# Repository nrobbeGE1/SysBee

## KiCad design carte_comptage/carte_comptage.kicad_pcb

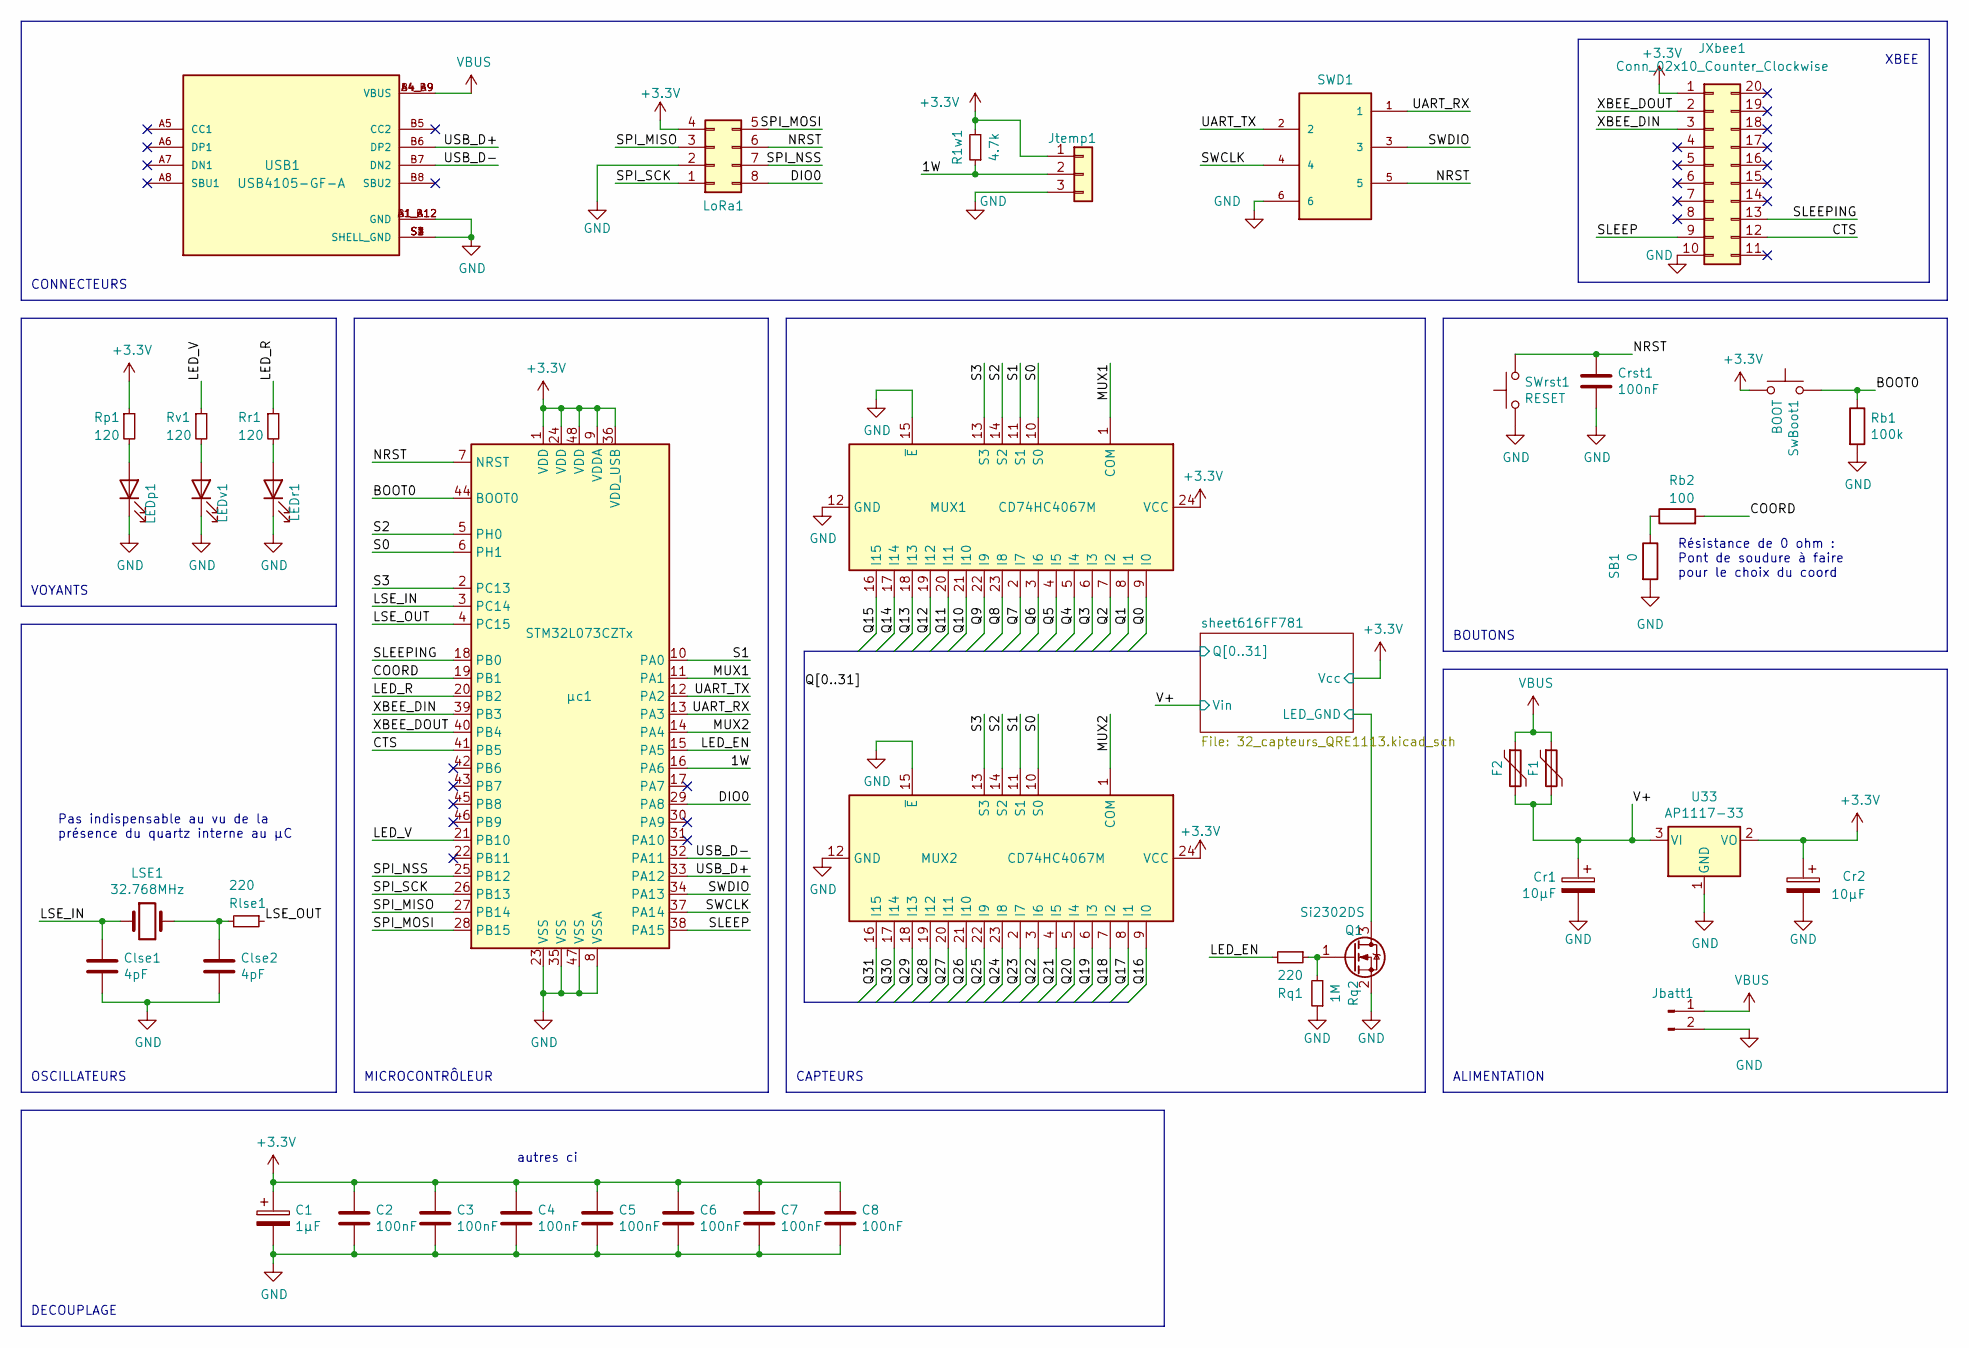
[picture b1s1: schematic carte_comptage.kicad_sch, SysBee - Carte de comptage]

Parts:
C1: 1µF; C_1206_3216Metric
C2, C3, C4, C5, C6, C7, C8: 100nF; C_1206_3216Metric
Clse1, Clse2: 4pF; C_1206_3216Metric
Cr1, Cr2: 10µF; CP_EIA-3216-18_Kemet-A
Crst1: 100nF; C_1206_3216Metric
F1, F2: Polyfuse; R_1206_3216Metric
JXbee1: Conn_02x10_Counter_Clockwise; Connector_Xbee
Jbatt1: Conn_01x02_Male; JST_PH_B2B-PH-K_1x02_P2.00mm_Vertical
Jtemp1: 1 WIRE; JST_PH_B3B-PH-K_1x03_P2.00mm_Vertical
LEDp1: LED; D_1206_3216Metric
LEDr1: LED; D_1206_3216Metric
LEDv1: LED; D_1206_3216Metric
LSE1: 32.768MHz; Crystal_SMD_2012-2Pin_2.0x1.2mm
LoRa1: Conn_02x04_Counter_Clockwise; ConnectorMicromatch-8
MUX1, MUX2: CD74HC4067M; SOIC-24W_7.5x15.4mm_P1.27mm
Q1: Si2302DS; SOT-23
R1w1: 4.7k; R_1206_3216Metric
Rb1: 100k; R_1206_3216Metric
Rb2: 100; R_1206_3216Metric
Rlse1: 220; R_1206_3216Metric
Rp1: 120; R_1206_3216Metric
Rq1: 220; R_1206_3216Metric
Rq2: 1M; R_1206_3216Metric
Rr1: 120; R_1206_3216Metric
Rv1: 120; R_1206_3216Metric
SB1: 0; SolderJumper-2_P1.3mm_Open_TrianglePad1.0x1.5mm
SWD1: SWD; TE_7-188275-6
SWrst1: RESET; PinHeader_1x02_P2.54mm_Vertical
SwBoot1: BOOT; PinHeader_1x02_P2.54mm_Vertical
U33: AP1117-33; SOT-223-3_TabPin2
USB1: USB4105-GF-A; GCT_USB4105-GF-A; PARTREV A3
µc1: STM32L073CZTx; LQFP-48_7x7mm_P0.5mm

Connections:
+3V3: C1.1, C2.1, C3.1, C4.1, C5.1, C6.1, C7.1, C8.1, Cr2.1, JXbee1.1, Jtemp1.1, LoRa1.4, MUX1.24 (VCC), MUX2.24 (VCC), R1w1.2, Rp1.1, SwBoot1.1, U33.2 (VO), µc1.1 (VDD), µc1.9 (VDDA), µc1.24 (VDD), µc1.36 (VDD_USB), µc1.48 (VDD); also elsewhere on the board
/1W: Jtemp1.2, R1w1.1, µc1.16 (PA6)
/BOOT0: Rb1.1, SwBoot1.2, µc1.44 (BOOT0)
/COORD: Rb2.2, µc1.19 (PB1)
/CTS: JXbee1.12, µc1.41 (PB5)
/DIO0: LoRa1.8, µc1.29 (PA8)
/LED_EN: Rq1.2, µc1.15 (PA5)
/LED_R: Rr1.1, µc1.20 (PB2)
/LED_V: Rv1.1, µc1.21 (PB10)
/LSE_IN: Clse1.1, LSE1.1, µc1.3 (PC14)
/LSE_OUT: Rlse1.1, µc1.4 (PC15)
/MUX1: MUX1.1 (COM), µc1.11 (PA1)
/MUX2: MUX2.1 (COM), µc1.14 (PA4)
/NRST: Crst1.1, LoRa1.6, SWD1.5, SWrst1.2, µc1.7 (NRST)
/Q0: MUX1.9 (I0); also elsewhere on the board
/Q1: MUX1.8 (I1); also elsewhere on the board
/Q2: MUX1.7 (I2); also elsewhere on the board
/Q3: MUX1.6 (I3); also elsewhere on the board
/Q4: MUX1.5 (I4); also elsewhere on the board
/Q5: MUX1.4 (I5); also elsewhere on the board
/Q6: MUX1.3 (I6); also elsewhere on the board
/Q7: MUX1.2 (I7); also elsewhere on the board
/Q8: MUX1.23 (I8); also elsewhere on the board
/Q9: MUX1.22 (I9); also elsewhere on the board
/Q10: MUX1.21 (I10); also elsewhere on the board
/Q11: MUX1.20 (I11); also elsewhere on the board
/Q12: MUX1.19 (I12); also elsewhere on the board
/Q13: MUX1.18 (I13); also elsewhere on the board
/Q14: MUX1.17 (I14); also elsewhere on the board
/Q15: MUX1.16 (I15); also elsewhere on the board
/Q16: MUX2.9 (I0); also elsewhere on the board
/Q17: MUX2.8 (I1); also elsewhere on the board
/Q18: MUX2.7 (I2); also elsewhere on the board
/Q19: MUX2.6 (I3); also elsewhere on the board
/Q20: MUX2.5 (I4); also elsewhere on the board
/Q21: MUX2.4 (I5); also elsewhere on the board
/Q22: MUX2.3 (I6); also elsewhere on the board
/Q23: MUX2.2 (I7); also elsewhere on the board
/Q24: MUX2.23 (I8); also elsewhere on the board
/Q25: MUX2.22 (I9); also elsewhere on the board
/Q26: MUX2.21 (I10); also elsewhere on the board
/Q27: MUX2.20 (I11); also elsewhere on the board
/Q28: MUX2.19 (I12); also elsewhere on the board
/Q29: MUX2.18 (I13); also elsewhere on the board
/Q30: MUX2.17 (I14); also elsewhere on the board
/Q31: MUX2.16 (I15); also elsewhere on the board
/S0: MUX1.10 (S0), MUX2.10 (S0), µc1.6 (PH1)
/S1: MUX1.11 (S1), MUX2.11 (S1), µc1.10 (PA0)
/S2: MUX1.14 (S2), MUX2.14 (S2), µc1.5 (PH0)
/S3: MUX1.13 (S3), MUX2.13 (S3), µc1.2 (PC13)
/SLEEP: JXbee1.9, µc1.38 (PA15)
/SLEEPING: JXbee1.13, µc1.18 (PB0)
/SPI_MISO: LoRa1.3, µc1.27 (PB14)
/SPI_MOSI: LoRa1.5, µc1.28 (PB15)
/SPI_NSS: LoRa1.7, µc1.25 (PB12)
/SPI_SCK: LoRa1.1, µc1.26 (PB13)
/SWCLK: SWD1.4, µc1.37 (PA14)
/SWDIO: SWD1.3, µc1.34 (PA13)
/UART_RX: SWD1.1, µc1.13 (PA3)
/UART_TX: SWD1.2, µc1.12 (PA2)
/USB_D+: USB1.B6 (DP2), µc1.33 (PA12)
/USB_D-: USB1.B7 (DN2), µc1.32 (PA11)
/V+: Cr1.1, F1.2, F2.2, U33.3 (VI); also elsewhere on the board
/XBEE_DIN: JXbee1.3, µc1.39 (PB3)
/XBEE_DOUT: JXbee1.2, µc1.40 (PB4)
/sheet616FF781/LED_GND: Q1.3 (D); also elsewhere on the board
GND: C1.2, C2.2, C3.2, C4.2, C5.2, C6.2, C7.2, C8.2, Clse1.2, Clse2.2, Cr1.2, Cr2.2, Crst1.2, JXbee1.10, Jbatt1.2, Jtemp1.3, LEDp1.1 (K), LEDr1.1 (K), LEDv1.1 (K), LoRa1.2, MUX1.12 (GND), MUX1.15 (~E), MUX2.12 (GND), MUX2.15 (~E), Q1.2 (S), Rb1.2, Rq2.1, SB1.2, SWD1.6, SWrst1.1, U33.1 (GND), USB1.A1_B12 (GND), USB1.B1_A12 (GND), USB1.S1 (SHELL_GND), USB1.S2 (SHELL_GND), USB1.S3 (SHELL_GND), USB1.S4 (SHELL_GND), µc1.8 (VSSA), µc1.23 (VSS), µc1.35 (VSS), µc1.47 (VSS); also elsewhere on the board
unnamed: Clse2.1, LSE1.2, Rlse1.2
unnamed: LEDp1.2 (A), Rp1.2
unnamed: LEDr1.2 (A), Rr1.2
unnamed: LEDv1.2 (A), Rv1.2
unnamed: Q1.1 (G), Rq1.1, Rq2.2
unnamed: Rb2.1, SB1.1
VBUS: F1.1, F2.1, Jbatt1.1, USB1.A4_B9 (VBUS), USB1.B4_A9 (VBUS)

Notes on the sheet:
OSCILLATEURS
DECOUPLAGE
ALIMENTATION
VOYANTS
BOUTONS
Résistance de 0 ohm : Pont de soudure à faire pour le choix du coord
CONNECTEURS
MICROCONTRÔLEUR
autres ci
Pas indispensable au vu de la présence du quartz interne au µC
XBEE
CAPTEURS

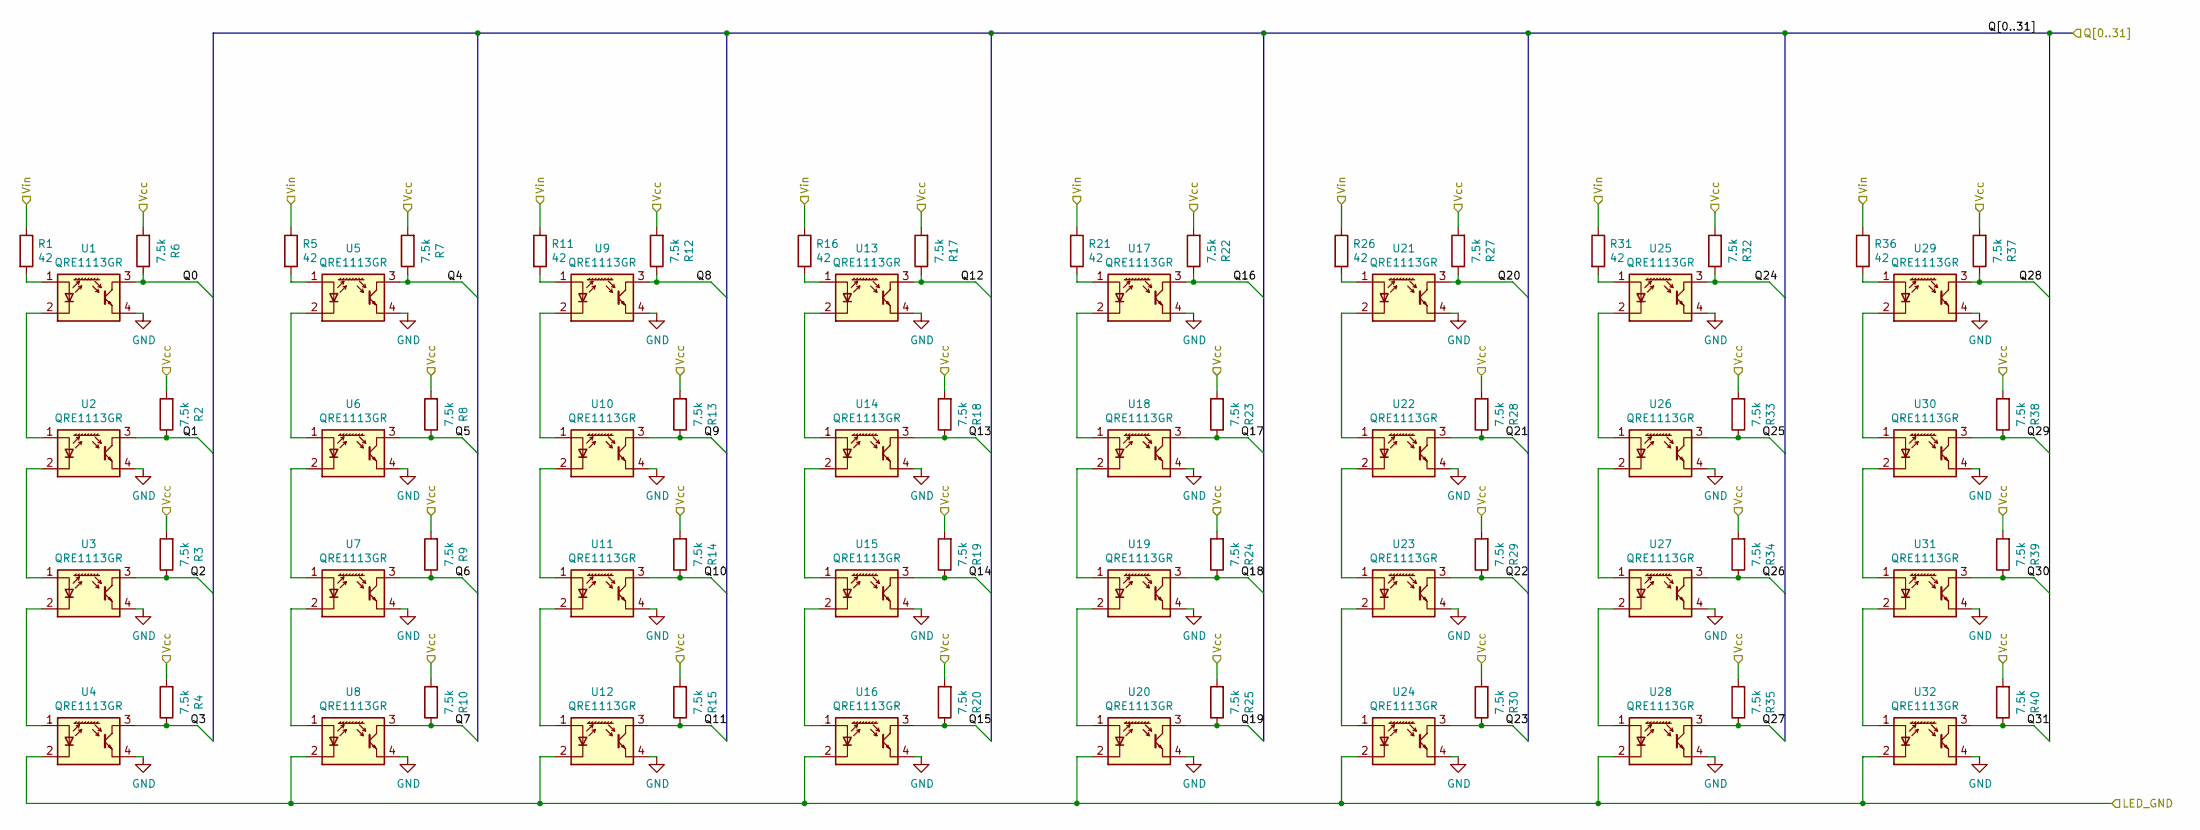
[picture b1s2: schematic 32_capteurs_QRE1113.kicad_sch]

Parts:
R1, R5, R11, R16, R21, R26, R31, R36: 42; R_1206_3216Metric
R2, R3, R4, R6, R7, R8, R9, R10, R12, R13, R14, R15, R17, R18, R19, R20, R22, R23, R24, R25, R27, R28, R29, R30, R32, R33, R34, R35, R37, R38, R39, R40: 7.5k; R_1206_3216Metric
U1, U2, U3, U4, U5, U6, U7, U8, U9, U10, U11, U12, U13, U14, U15, U16, U17, U18, U19, U20, U21, U22, U23, U24, U25, U26, U27, U28, U29, U30, U31, U32: QRE1113GR; OnSemi_CASE100CY

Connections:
+3V3: R2.2, R3.2, R4.2, R6.2, R7.2, R8.2, R9.2, R10.2, R12.2, R13.2, R14.2, R15.2, R17.2, R18.2, R19.2, R20.2, R22.2, R23.2, R24.2, R25.2, R27.2, R28.2, R29.2, R30.2, R32.2, R33.2, R34.2, R35.2, R37.2, R38.2, R39.2, R40.2; also elsewhere on the board
/Q0: R6.1, U1.3; also elsewhere on the board
/Q1: R2.1, U2.3; also elsewhere on the board
/Q2: R3.1, U3.3; also elsewhere on the board
/Q3: R4.1, U4.3; also elsewhere on the board
/Q4: R7.1, U5.3; also elsewhere on the board
/Q5: R8.1, U6.3; also elsewhere on the board
/Q6: R9.1, U7.3; also elsewhere on the board
/Q7: R10.1, U8.3; also elsewhere on the board
/Q8: R12.1, U9.3; also elsewhere on the board
/Q9: R13.1, U10.3; also elsewhere on the board
/Q10: R14.1, U11.3; also elsewhere on the board
/Q11: R15.1, U12.3; also elsewhere on the board
/Q12: R17.1, U13.3; also elsewhere on the board
/Q13: R18.1, U14.3; also elsewhere on the board
/Q14: R19.1, U15.3; also elsewhere on the board
/Q15: R20.1, U16.3; also elsewhere on the board
/Q16: R22.1, U17.3; also elsewhere on the board
/Q17: R23.1, U18.3; also elsewhere on the board
/Q18: R24.1, U19.3; also elsewhere on the board
/Q19: R25.1, U20.3; also elsewhere on the board
/Q20: R27.1, U21.3; also elsewhere on the board
/Q21: R28.1, U22.3; also elsewhere on the board
/Q22: R29.1, U23.3; also elsewhere on the board
/Q23: R30.1, U24.3; also elsewhere on the board
/Q24: R32.1, U25.3; also elsewhere on the board
/Q25: R33.1, U26.3; also elsewhere on the board
/Q26: R34.1, U27.3; also elsewhere on the board
/Q27: R35.1, U28.3; also elsewhere on the board
/Q28: R37.1, U29.3; also elsewhere on the board
/Q29: R38.1, U30.3; also elsewhere on the board
/Q30: R39.1, U31.3; also elsewhere on the board
/Q31: R40.1, U32.3; also elsewhere on the board
/V+: R1.1, R5.1, R11.1, R16.1, R21.1, R26.1, R31.1, R36.1; also elsewhere on the board
/sheet616FF781/LED_GND: U4.2 (K), U8.2 (K), U12.2 (K), U16.2 (K), U20.2 (K), U24.2 (K), U28.2 (K), U32.2 (K); also elsewhere on the board
GND: U1.4, U2.4, U3.4, U4.4, U5.4, U6.4, U7.4, U8.4, U9.4, U10.4, U11.4, U12.4, U13.4, U14.4, U15.4, U16.4, U17.4, U18.4, U19.4, U20.4, U21.4, U22.4, U23.4, U24.4, U25.4, U26.4, U27.4, U28.4, U29.4, U30.4, U31.4, U32.4; also elsewhere on the board
unnamed: R1.2, U1.1 (A)
unnamed: R5.2, U5.1 (A)
unnamed: R11.2, U9.1 (A)
unnamed: R16.2, U13.1 (A)
unnamed: R21.2, U17.1 (A)
unnamed: R26.2, U21.1 (A)
unnamed: R31.2, U25.1 (A)
unnamed: R36.2, U29.1 (A)
unnamed: U1.2 (K), U2.1 (A)
unnamed: U2.2 (K), U3.1 (A)
unnamed: U3.2 (K), U4.1 (A)
unnamed: U5.2 (K), U6.1 (A)
unnamed: U6.2 (K), U7.1 (A)
unnamed: U7.2 (K), U8.1 (A)
unnamed: U9.2 (K), U10.1 (A)
unnamed: U10.2 (K), U11.1 (A)
unnamed: U11.2 (K), U12.1 (A)
unnamed: U13.2 (K), U14.1 (A)
unnamed: U14.2 (K), U15.1 (A)
unnamed: U15.2 (K), U16.1 (A)
unnamed: U17.2 (K), U18.1 (A)
unnamed: U18.2 (K), U19.1 (A)
unnamed: U19.2 (K), U20.1 (A)
unnamed: U21.2 (K), U22.1 (A)
unnamed: U22.2 (K), U23.1 (A)
unnamed: U23.2 (K), U24.1 (A)
unnamed: U25.2 (K), U26.1 (A)
unnamed: U26.2 (K), U27.1 (A)
unnamed: U27.2 (K), U28.1 (A)
unnamed: U29.2 (K), U30.1 (A)
unnamed: U30.2 (K), U31.1 (A)
unnamed: U31.2 (K), U32.1 (A)

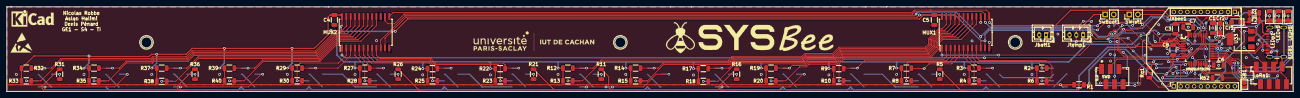
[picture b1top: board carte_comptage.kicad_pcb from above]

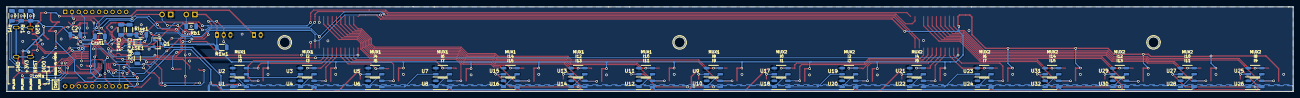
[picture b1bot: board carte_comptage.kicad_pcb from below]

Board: 2 copper layers, 380.0 x 25.0 mm, 115 parts (45 on the bottom side), 106 nets.

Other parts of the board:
Ref**: Val**; drawing

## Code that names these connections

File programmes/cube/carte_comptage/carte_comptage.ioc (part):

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Mcu.Name=STM32L073C(B-Z)Tx
Mcu.Package=LQFP48
Mcu.UserName=STM32L073CZTx
PA0.GPIOParameters=GPIO_Label
PA0.GPIO_Label=S1
PA0.Signal=GPIO_Output
PA1.GPIOParameters=GPIO_Label
PA1.GPIO_Label=MUX1
PA1.Signal=GPIO_Input
PA11.Mode=Device
PA11.Signal=USB_DM
PA12.Mode=Device
PA12.Signal=USB_DP
PA13.Mode=Serial_Wire
PA13.Signal=SYS_SWDIO
PA14.Mode=Serial_Wire
PA14.Signal=SYS_SWCLK
PA15.GPIOParameters=GPIO_Label
PA15.GPIO_Label=XBEE_SLEEP
PA15.Signal=GPIO_Output
PA2.Mode=Asynchronous
PA2.Signal=USART2_TX
PA3.Mode=Asynchronous
PA3.Signal=USART2_RX
PA4.GPIOParameters=GPIO_Label
PA4.GPIO_Label=MUX2
PA4.Signal=GPIO_Input
PA5.GPIOParameters=GPIO_Label
PA5.GPIO_Label=LED_EN
PA5.Signal=GPIO_Output
PA6.GPIOParameters=GPIO_Label
PA6.GPIO_Label=ONE_WIRE
PA6.Signal=GPIO_Input
PA8.GPIOParameters=GPIO_Label
PA8.GPIO_Label=DIO0
PA8.Signal=GPIO_Output
PB0.GPIOParameters=GPIO_Label
PB0.GPIO_Label=XBEE_SLEEPING
PB0.Signal=GPIO_Input
PB10.GPIOParameters=GPIO_Label
PB10.GPIO_Label=LED_V
PB10.Signal=GPIO_Output
PB11.GPIOParameters=GPIO_Label
PB11.GPIO_Label=ONE_WIRE
PB11.Signal=GPIO_Output
PB12.Mode=NSS_Signal_Hard_Output
PB12.Signal=SPI2_NSS
PB13.Mode=Full_Duplex_Master
PB13.Signal=SPI2_SCK
PB14.Mode=Full_Duplex_Master
PB14.Signal=SPI2_MISO
PB15.Mode=Full_Duplex_Master
PB15.Signal=SPI2_MOSI
PB2.GPIOParameters=GPIO_Label
PB2.GPIO_Label=LED_R
PB2.Signal=GPIO_Output
PB3.Mode=Asynchronous
PB3.Signal=USART5_TX
PB4.Mode=Asynchronous
PB4.Signal=USART5_RX
PC13.GPIOParameters=GPIO_Label
PC13.GPIO_Label=S3
PC13.Signal=GPIO_Output
PC14-OSC32_IN.Mode=LSE-External-Oscillator
PC14-OSC32_IN.Signal=RCC_OSC32_IN
PC15-OSC32_OUT.Mode=LSE-External-Oscillator
PC15-OSC32_OUT.Signal=RCC_OSC32_OUT
PH0-OSC_IN.GPIOParameters=GPIO_Label
PH0-OSC_IN.GPIO_Label=S2
PH0-OSC_IN.Signal=GPIO_Output
PH1-OSC_OUT.GPIOParameters=GPIO_Label
PH1-OSC_OUT.GPIO_Label=S0
PH1-OSC_OUT.Signal=GPIO_Output
RCC.HSE_VALUE=16000000
RCC.SYSCLKFreq_VALUE=16000000
RCC.SYSCLKSource=RCC_SYSCLKSOURCE_HSI
board=custom

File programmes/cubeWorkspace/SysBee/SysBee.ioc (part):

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Mcu.Name=STM32L073C(B-Z)Tx
Mcu.Package=LQFP48
Mcu.UserName=STM32L073CZTx
PA0.GPIOParameters=GPIO_Label
PA0.GPIO_Label=S1
PA0.Signal=GPIO_Output
PA1.GPIOParameters=GPIO_Label
PA1.GPIO_Label=MUX1
PA1.Mode=IN1
PA1.Signal=ADC_IN1
PA10.GPIOParameters=GPIO_Label
PA10.GPIO_Label=USART_XBEE_RX
PA10.Mode=Asynchronous
PA10.Signal=USART1_RX
PA2.GPIOParameters=GPIO_Label
PA2.GPIO_Label=UART_TX
PA2.Mode=Asynchronous
PA2.Signal=USART2_TX
PA3.GPIOParameters=GPIO_Label
PA3.GPIO_Label=UART_RX
PA3.Mode=Asynchronous
PA3.Signal=USART2_RX
PA4.GPIOParameters=GPIO_Label
PA4.GPIO_Label=MUX2
PA4.Mode=IN4
PA4.Signal=ADC_IN4
PA5.GPIOParameters=GPIO_Label
PA5.GPIO_Label=LED_EN
PA5.Signal=GPIO_Output
PA9.GPIOParameters=GPIO_Label
PA9.GPIO_Label=USART_XBEE_TX
PA9.Mode=Asynchronous
PA9.Signal=USART1_TX
PB10.GPIOParameters=GPIO_Label
PB10.GPIO_Label=LED_V
PB10.Signal=GPIO_Output
PB2.GPIOParameters=GPIO_Label
PB2.GPIO_Label=LED_R
PB2.Signal=GPIO_Output
PC13.GPIOParameters=GPIO_Label
PC13.GPIO_Label=S3
PC13.Signal=GPIO_Output
PH0-OSC_IN.GPIOParameters=GPIO_Label
PH0-OSC_IN.GPIO_Label=S2
PH0-OSC_IN.Signal=GPIO_Output
PH1-OSC_OUT.GPIOParameters=GPIO_Label
PH1-OSC_OUT.GPIO_Label=S0
PH1-OSC_OUT.Signal=GPIO_Output
RCC.HSE_VALUE=8000000
RCC.SYSCLKFreq_VALUE=2097000
board=custom

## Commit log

2021-09-03 test carte comptage, il faut démarrer les projets stm32cube
2021-09-03 nvl essai envoyer début kicad
2021-09-03 test fini de [modifier readme]
    mais il faut toujours faire cette partie ....
2021-09-03 Application android
2021-09-03 test
2021-09-03 debut partie buck
2021-09-05 ajouté buck au schéma
2021-09-05 test sans push
2021-09-05 carte comptage SWD
2021-09-06 debut xtal a finir
2021-09-06 ajouté capteurs et réorganisé schéma
2021-09-07 projet cubeMX et connexions Xbee
2021-09-07 finif xtal et connecteur xbee, peut etre port 1 wire
2021-09-12 Prêt à commencer le routage
2021-09-14 Début assignation empruntes
2021-09-14 14.09
2021-09-15 pret à router
2021-09-16 Adaptateur lora
2021-09-16 debut routage
2021-09-19 Routage fini, à vérifier, ajouter les encoches de montage
2021-09-20 ajouter trous
2021-09-21 trous finis, exporter eurocircuit et FreeCAD
2021-09-21 carte à vérifier
2021-09-21 debut code xbee+stm32
2021-09-22 automate de reception frame xbee, terminer les adresses et option
2021-09-22 code xbee
2021-09-23 23.09.2021
2021-09-24 fini reception AT
2021-09-27 fini envoi des parametres xbee
2021-10-12 code qui fonctionnait hier
2021-10-12 nickel prog xbee
2021-10-15 15.10.2021
2021-10-16 Signaux visuels et déclenchement d'une alerte à distance
2022-01-22 fonctionne à nouveau
    programmation automatique du xBee
    routeurs envoient l’alerte au coordinateur
    signal lumineux alerte si on reçoit une alerte
    réparé le buffer de lecture --> lit du premier coup au lieux du deuxieme
    (à étudier si c'est pas intéressant de faire des alertes récurrentes jusqu'à un acknowledge plutôt qu'une seule, au cas où elle est pas passée)
    reset à distance
2022-01-25 Create 0_S4p2021_Rapport_SysBee_Petrean_Sengchan_Serry_Decieux.pdf
    ajout rapport de projet de l'an dernier
2022-01-25 ajout obsidian
2022-01-25 bim bim ça progresse
2022-01-27 avancée 27/01
    ajout notes obsidian
2022-01-27 ajout commentaires
    compréhension + ajout commentaires automate de config xbee
2022-01-27 Create nico
2022-01-27 delete nico
    j'ai supprimé nico il m'a trop soulé
2022-01-28 ajout images + notes
2022-02-03 ajout obsidian programme receivetoidle_dma
2022-02-03 rangement obsidian
2022-02-03 rangement obsidian (suite)
2022-02-04 maj obsidian
2022-02-15 pcb ok
2022-02-15 ajout jumper coordinateur pcb
2022-03-11 carte capteur finie
2022-03-11 début CAD
2022-03-11 fix déplacement silkscreen
2022-03-30 proto boitier
2022-03-31 avance programme
2022-03-31 bon dossier
2022-04-04 comptage ok sur un capteur, à scaler
2022-04-13 lecture analogique WIP
2022-04-20 fin du cadre projet S4 strict
